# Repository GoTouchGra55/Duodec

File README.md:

# Duodec

A 12-key + 1 rotary encoder macropad built on
the RP2040-Zero, designed for developers and
students who live in their terminal.

---

## Overview

**Duodec** (Latin: _twelve_) is a compact, open-source macropad featuring 12 mechanical switches, a clickable rotary encoder, and an 128x32 OLED display. Built around the RP2040-Zero, it's fully programmable in Python.

---

## Working Demo

Here’s a quick demonstration of Duodec in action, showing key inputs, encoder rotation, and OLED layer switching.

---

## Features

- 12x mechanical key switches in a 4x3 matrix
- 1x rotary encoder with push-button click
- 128x32 OLED display
- RP2040-Zero (RP2040 chip, USB-C)
- Fully programmable in Python
- Multiple layers for different workflows
- Custom 3D printed keys
- Open source hardware and software

## ⚠️ Important Wiring Note
Sorry about this ;-; but the OLED display requires **2-4kΩ 3.3V pull-up resistors** on both:
- SDA (I2C data line)
- SCL (I2C clock line)

Without these, the display will not function at all.

## Customization

1. Clone this repository
2. Open `src/main.py`
3. Modify keymaps (line 26)
4. Add your own shortcuts and layers
5. Flash to your RP2040-Zero

Be productive 🚀

## Contributing

Contributions are welcome!

If you'd like to improve Duodec, you can:
- Suggest new features or workflows
- Improve firmware or add new layers
- Fix bugs or optimize performance
- Enhance documentation or visuals

Please open an issue first to discuss major changes.

Pull requests should be clean, well-documented, and tested where possible.

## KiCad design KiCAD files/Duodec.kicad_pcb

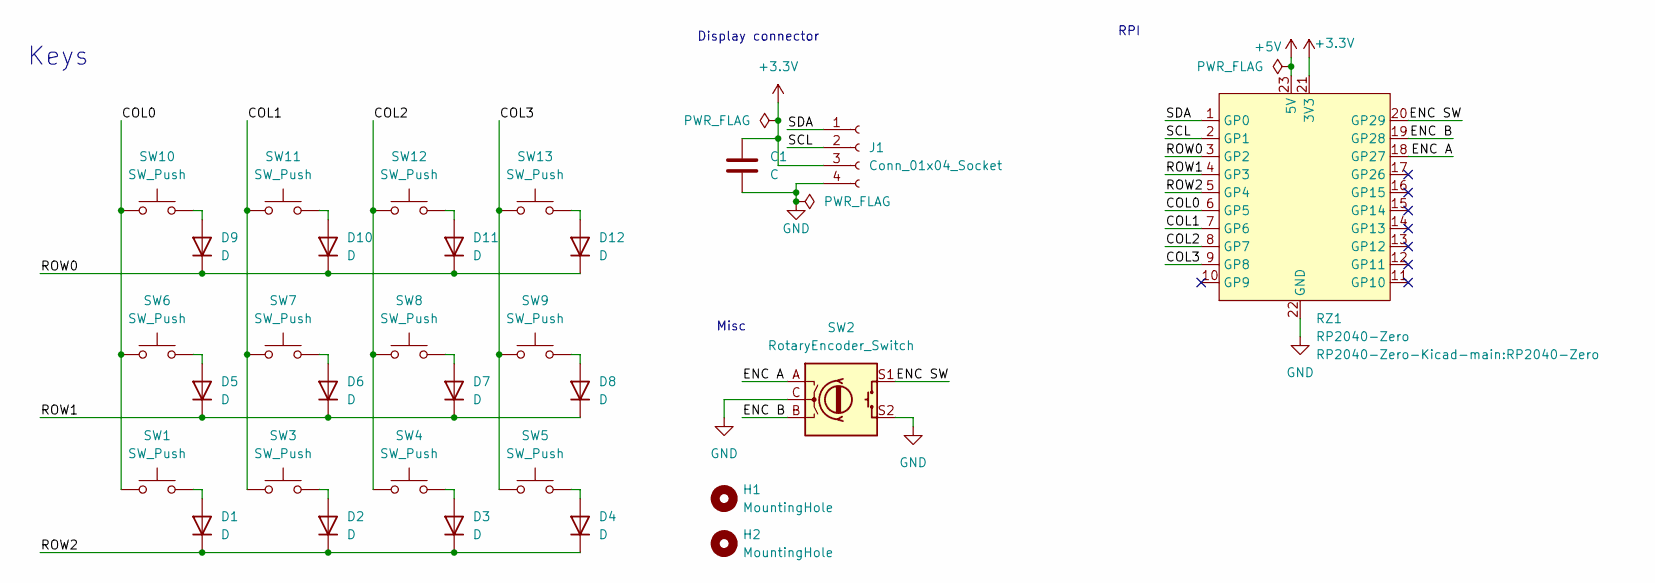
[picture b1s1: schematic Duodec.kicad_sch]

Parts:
C1: C; C_0402_1005Metric
D1, D2, D3, D4, D5, D6, D7, D8, D9, D10, D11, D12: D; D_SOD-123
H1, H2: MountingHole; MountingHole_3.2mm_M3
J1: Conn_01x04_Socket; PinSocket_1x04_P2.54mm_Vertical
RZ1: RP2040-Zero
SW1, SW3, SW4, SW5, SW6, SW7, SW8, SW9, SW10, SW11, SW12, SW13: SW_Push; SW_Cherry_MX_PCB_1.00u
SW2: RotaryEncoder_Switch; RotaryEncoder_Duodec

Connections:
+3.3V: C1.1, J1.3, RZ1.21 (3V3)
+5V: RZ1.23 (5V)
/COL0: RZ1.6 (GP5), SW1.1, SW6.1, SW10.1
/COL1: RZ1.7 (GP6), SW3.1, SW7.1, SW11.1
/COL2: RZ1.8 (GP7), SW4.1, SW8.1, SW12.1
/COL3: RZ1.9 (GP8), SW5.1, SW9.1, SW13.1
/ENC A: RZ1.18 (GP27), SW2.A
/ENC B: RZ1.19 (GP28), SW2.B
/ENC SW: RZ1.20 (GP29), SW2.S1
/ROW0: D9.1 (K), D10.1 (K), D11.1 (K), D12.1 (K), RZ1.3 (GP2)
/ROW1: D5.1 (K), D6.1 (K), D7.1 (K), D8.1 (K), RZ1.4 (GP3)
/ROW2: D1.1 (K), D2.1 (K), D3.1 (K), D4.1 (K), RZ1.5 (GP4)
/SCL: J1.2, RZ1.2 (GP1)
/SDA: J1.1, RZ1.1 (GP0)
GND: C1.2, J1.4, RZ1.22 (GND), SW2.C, SW2.S2
unnamed: D1.2 (A), SW1.2
unnamed: D2.2 (A), SW3.2
unnamed: D3.2 (A), SW4.2
unnamed: D4.2 (A), SW5.2
unnamed: D5.2 (A), SW6.2
unnamed: D6.2 (A), SW7.2
unnamed: D7.2 (A), SW8.2
unnamed: D8.2 (A), SW9.2
unnamed: D9.2 (A), SW10.2
unnamed: D10.2 (A), SW11.2
unnamed: D11.2 (A), SW12.2
unnamed: D12.2 (A), SW13.2

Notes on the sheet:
Keys
Misc
Display connector
RPI

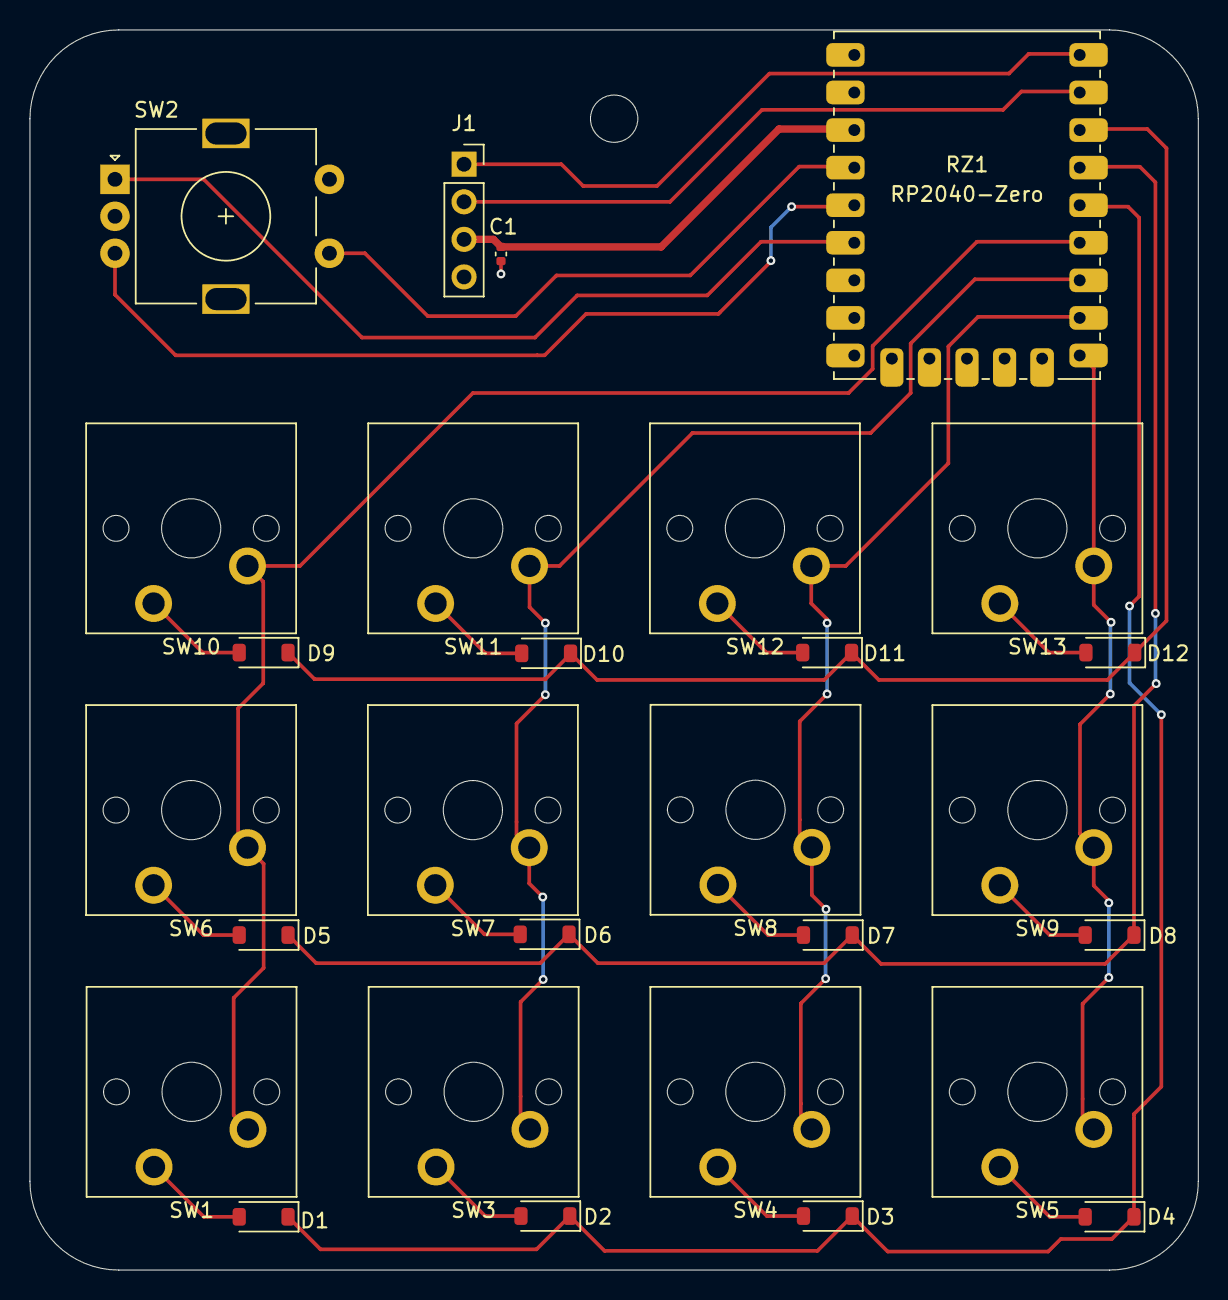
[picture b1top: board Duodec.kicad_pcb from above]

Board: 2 copper layers, 79.0 x 83.8 mm, 29 parts (0 on the bottom side), 26 nets.

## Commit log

2026-03-08 Add files
2026-03-13 Add test firmware
2026-03-13 Add CAD files and organize structure
2026-03-13 Add BOM
2026-03-14 Add kicad files
2026-03-18 Modify cost for PCB and 3D parts entry
    Updated the cost per item for PCB and 3D parts.
2026-03-18 Correct PCB and 3D Parts unit price
    Updated the unit price of PCB and 3D Parts from $30.76 to $17.59.
2026-04-26 Finish Duodec v1

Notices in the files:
README.md:
License: MIT
